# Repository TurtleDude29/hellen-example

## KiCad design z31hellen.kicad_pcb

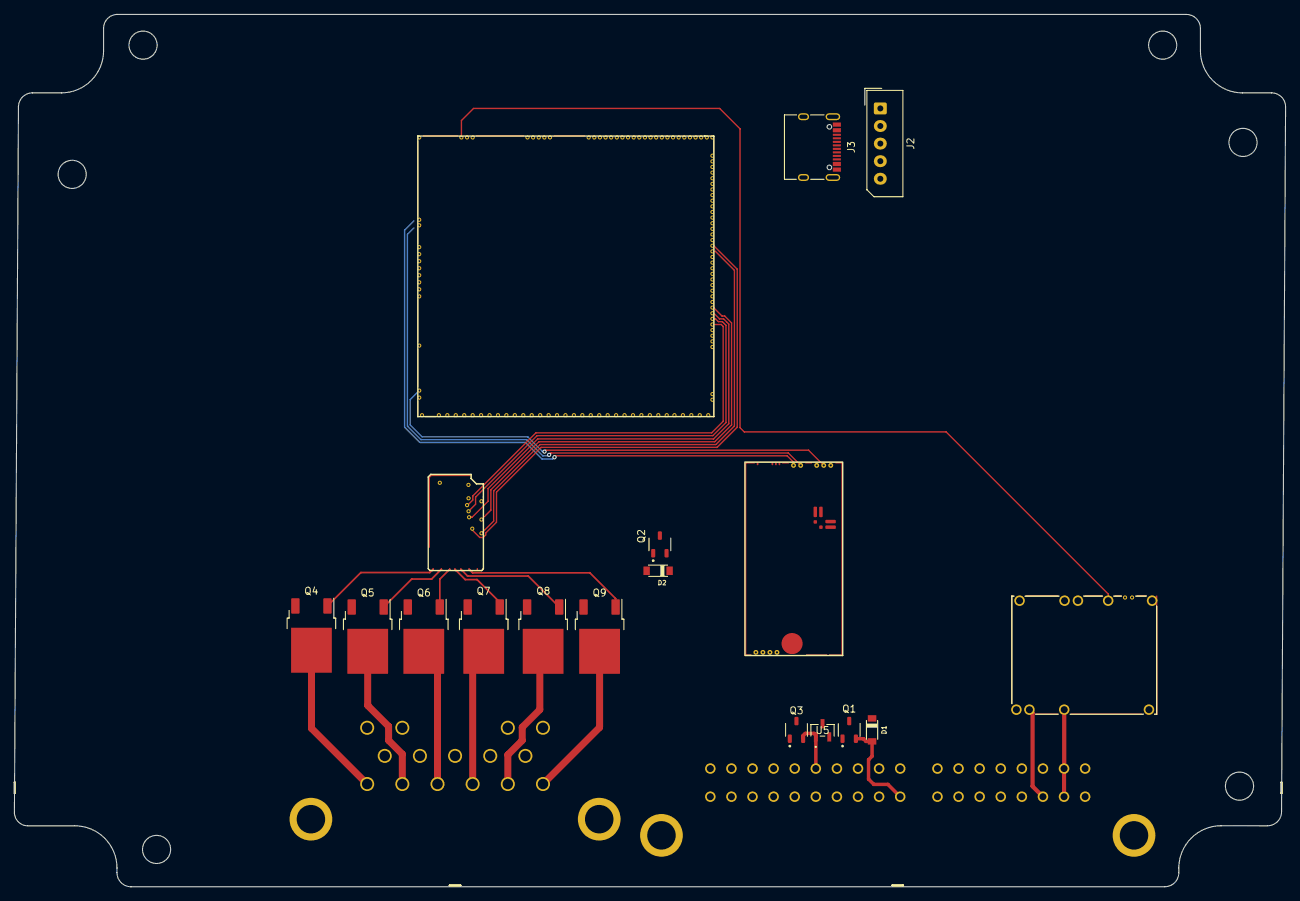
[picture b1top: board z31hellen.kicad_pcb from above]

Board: 4 copper layers, 180.8 x 124.1 mm, 19 parts (0 on the bottom side), 33 nets.

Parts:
D1, D2: B5819W-TP; SOD3716X135N
J2: Conn_01x05_Male; Molex_SPOX_5267-05A_1x05_P2.50mm_Vertical
J3: USB_C_Receptacle_USB2.0; USB_C_Receptacle_XKB_U262-16XN-4BVC11
M1: Module-mega-mcu144-0.6; mega-mcu144
M2: Module-power_12and5V-0.2; power_12and5V
M3: Module-wbo-0.5; wbo
M4: Module-ign8-0.2; ign8
Q1, Q2, Q3: AO3400A; SOT95P280X125-3N
Q4, Q5, Q6, Q7, Q8, Q9: VND14NV04-E; DPAK
U5: PSM712-LF-T7; SOT_12-LF-T7_PTD
Z1: Z31 15 + 36

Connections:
+5V: M1.N31 (VCC), M2.E4 (V5)
+5VA: M1.W2 (V5A_SWITCHABLE), M3.W1 (V5_IN)
/12v Switched: M2.V2 (IN_VIGN), Z1.34
/FP RELAY: D1.A, Q1.2, Z1.20
/INJ 1: Q4.2 (D), Z1.101
/INJ 2: Q5.2 (D), Z1.102
/INJ 3: Q6.2 (D), Z1.103
/INJ 4: Q7.2 (D), Z1.104
/INJ 5: Q8.2 (D), Z1.105
/INJ 6: Q9.2 (D), Z1.106
/Injectors/INJ_MCU_1: M4.S8 (OUT_IGN1), Q4.1 (IN)
/Injectors/INJ_MCU_2: M4.S7 (OUT_IGN2), Q5.1 (IN)
/Injectors/INJ_MCU_3: M4.S6 (OUT_IGN3), Q6.1 (IN)
/Injectors/INJ_MCU_4: M4.S5 (OUT_IGN4), Q7.1 (IN)
/Injectors/INJ_MCU_5: M4.S4 (OUT_IGN5), Q8.1 (IN)
/Injectors/INJ_MCU_6: M4.S3 (OUT_IGN6), Q9.1 (IN)
/LOWSIDE WEAK/FP_MCU: M1.E8 (OUT_IO1), Q1.1
/LOWSIDE WEAK/MR_MCU(HOT): M1.E12 (OUT_IO2), Q3.1
/LOWSIDE WEAK/MR_OUT(HOT): Q3.2, U5.1, Z1.6
/LOWSIDE WEAK/OUT1: D2.A, Q2.2
/MEGA_MCU/INJ_MCU_1: M1.E19 (OUT_INJ1), M4.V8 (IGN1)
/MEGA_MCU/INJ_MCU_2: M1.E18 (OUT_INJ2), M4.V7 (IGN2)
/MEGA_MCU/INJ_MCU_3: M1.E29 (OUT_INJ3), M4.V6 (IGN3)
/MEGA_MCU/INJ_MCU_4: M1.E30 (OUT_INJ4), M4.V5 (IGN4)
/MEGA_MCU/INJ_MCU_5: M1.E31 (OUT_INJ5), M4.V4 (IGN5)
/MEGA_MCU/INJ_MCU_6: M1.E32 (OUT_INJ6), M4.V3 (IGN6)
/MEGA_MCU/USB+: J2.3, J3.A6 (D+), J3.B6 (D+), M1.N3 (USBP)
/MEGA_MCU/USB-: J2.2, J3.A7 (D-), J3.B7 (D-), M1.N2 (USBM)
/MEGA_MCU/VBUS: J2.1, J3.A4 (VBUS), J3.A9 (VBUS), J3.B4 (VBUS), J3.B9 (VBUS), M1.N4 (VBUS)
/Main Relay power: M2.V3 (V12_RAW), Z1.27, Z1.35
GND: J2.4, J2.5, J3.A1 (GND), J3.A12 (GND), J3.B1 (GND), J3.B12 (GND), J3.S1 (SHIELD), M1.G (GND), M2.S1 (GND), M3.E6 (LSU_H-), M3.G (GND), Q1.3, Q2.3, Q3.3, Q4.3 (S), Q5.3 (S), Q6.3 (S), Q7.3 (S), Q8.3 (S), Q9.3 (S), U5.2, Z1.26
GNDA: M1.E39 (GNDA), M1.W1 (GNDA)
unnamed: M3.J1 (SEL1), M3.J_GND1 (PULL_DOWN1)

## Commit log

2024-09-18 [skip actions] Auto-generated board v2.1
2024-09-18 Rename bom_replace_xxxyyy-a.csv to bom_replace_bom_replace_Z31HELLEN-a.csv
2024-09-18 Rename bom_replace_bom_replace_Z31HELLEN-a.csv to bom_replace_Z31HELLEN-a.csv
2024-10-04 GHA says update hellen-one
2024-12-12 Rename Z31HELLEN v3.kicad_pro to z31hellen.kicad_pro
2024-12-12 Rename Z31HELLEN v3.kicad_prl to z31hellen.kicad_prl
2024-12-12 Rename bom_replace_xxxyyy-a.csv to bom_replace_z31hellen-a.csv
2025-01-31 GHA says update kicad6-libraries
